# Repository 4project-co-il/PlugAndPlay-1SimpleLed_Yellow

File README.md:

# PlugAndPlay: Module with 1 simple blue LED
This is the repository with the files for PlugAndPlay module with 1 simple blue LED.

The LED is connected to interrupt line #1 of the PnP connector.

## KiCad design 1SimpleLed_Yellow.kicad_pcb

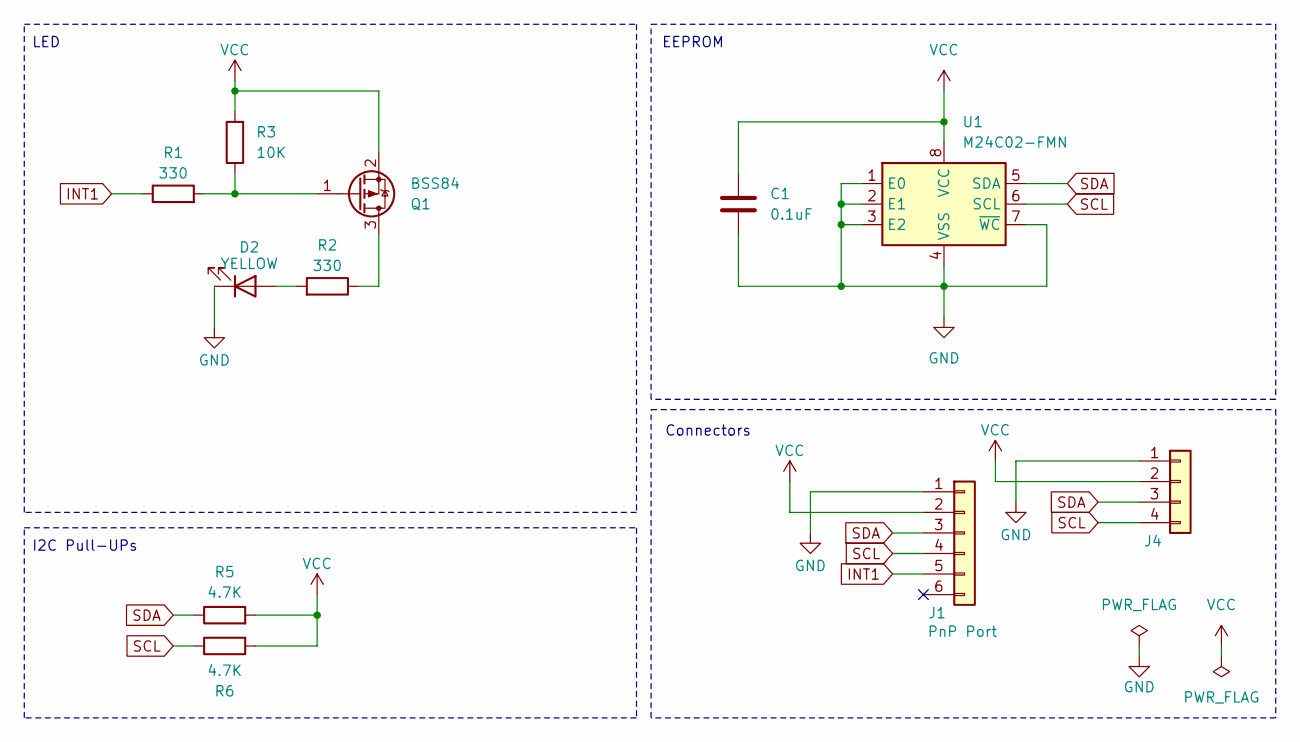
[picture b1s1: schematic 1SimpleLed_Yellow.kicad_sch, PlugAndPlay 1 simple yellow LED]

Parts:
C1: 0.1uF; C_0603_1608Metric; MPN C14663
D2: YELLOW; LED_0603_1608Metric; MPN C965802
J1: JST_SH_SM06B-SRSS-TB_1x06-1MP_P1.00mm_Horizontal; MPN C7430448
J4: Conn_01x04; PogoPinsPads_1x04_P2.5mm
Q1: BSS84; SOT-23; MPN C114481
R1, R2: 330; R_0603_1608Metric; MPN C23138
R3: 10K; R_0603_1608Metric; MPN C25804
R5, R6: 4.7K; R_0603_1608Metric; MPN C4190
U1: M24C02-FMN; SOIC-8_3.9x4.9mm_P1.27mm; MPN C114502

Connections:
GND: C1.2, D2.1 (K), J1.1, J4.1, U1.1 (E0), U1.2 (E1), U1.3 (E2), U1.4 (VSS), U1.7 (~WC)
INT1: J1.5, R1.1
unnamed: D2.2 (A), R2.2
unnamed: Q1.3 (D), R2.1
unnamed: Q1.1 (G), R1.2, R3.1
SCL: J1.4, J4.4, R6.1, U1.6 (SCL)
SDA: J1.3, J4.3, R5.1, U1.5 (SDA)
VCC: C1.1, J1.2, J4.2, Q1.2 (S), R3.2, R5.2, R6.2, U1.8 (VCC)

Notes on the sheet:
EEPROM
LED
Connectors
I2C Pull-UPs

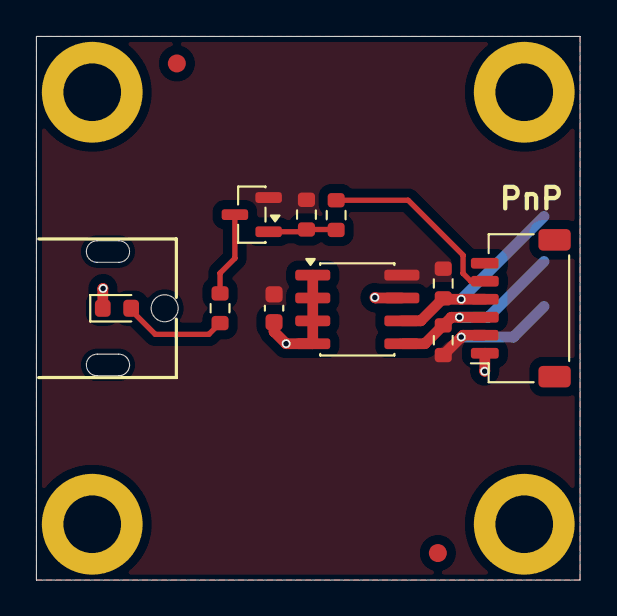
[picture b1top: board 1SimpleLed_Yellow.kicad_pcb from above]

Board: 2 copper layers, 30.2 x 30.2 mm, 11 parts (1 on the bottom side), 8 nets.
